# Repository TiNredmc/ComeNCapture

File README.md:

# ComeNCapture
This is very quick and dirty logic analyzer. Built with my sdcc template. https://github.com/TiNredmc/stm8l_sdcc_template/tree/master/code/ComeNCapture

# The Concept
<>

# Project status

Work in progress.

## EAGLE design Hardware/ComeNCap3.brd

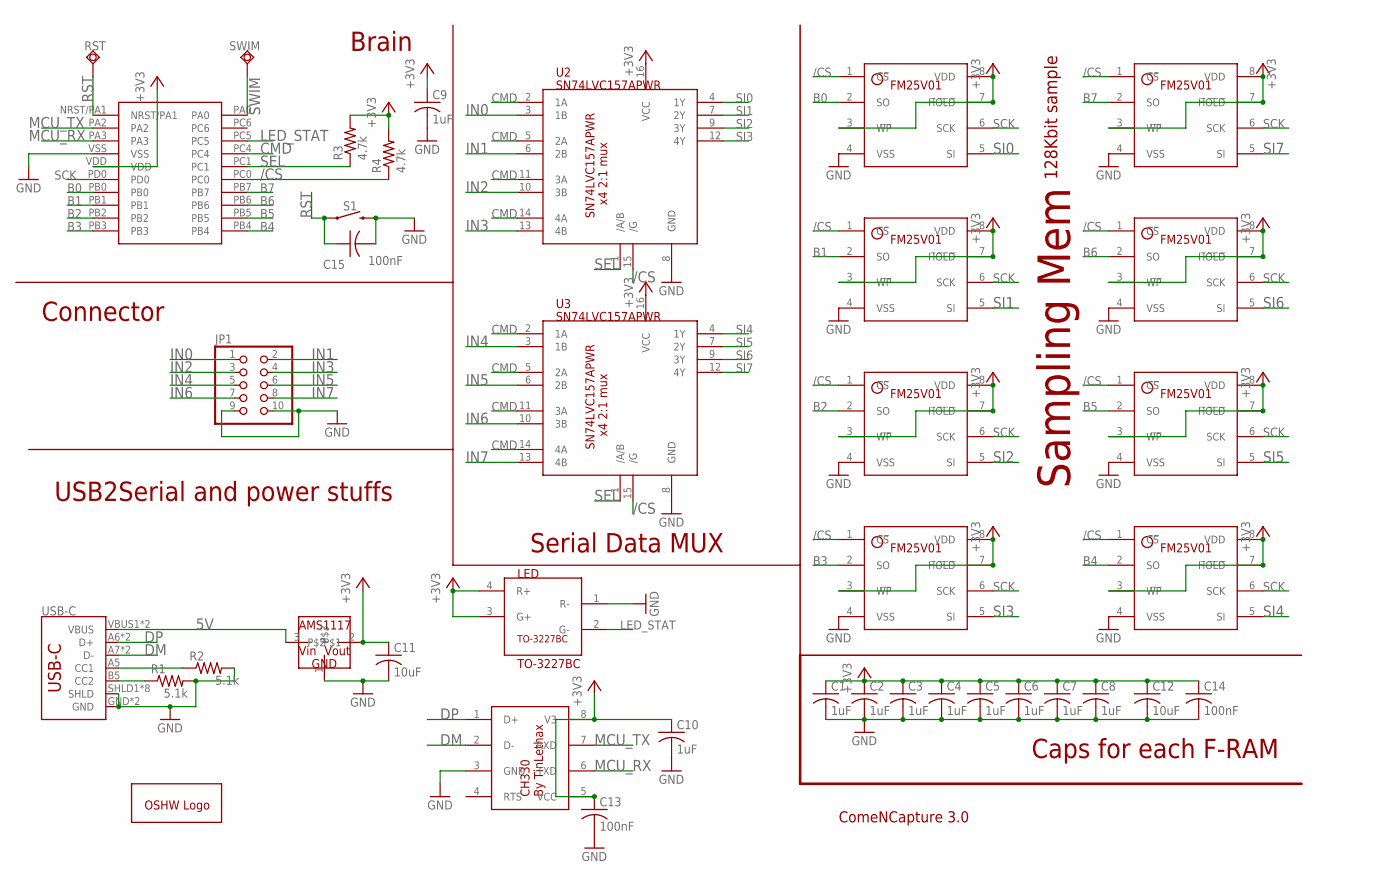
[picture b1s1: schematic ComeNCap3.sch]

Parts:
C1, C2, C3, C4, C5, C6, C7, C8, C9, C10: 1uF; C0603
C11, C12: 10uF; C0805
C13, C14, C15: 100nF; C1206
GOLD_ORB_SM1: OSHWLOGOLOGO5MM; OSHW_5MM
JP1: PINHD-2X5; 2X05
LED: TO-3227BC; DIODFN320X270X40-4L
M0, M1, M2, M3, M4, M5, M6, M7: FM25V01; SOIC127P601X172-8N
R1, R2: 5.1k; R0603
R3, R4: 4.7k; R0603
RST: TPSQTP20R; TP20R
S1: MOMENTARY-SWITCH-SPST-SMD-5.2-REDUNDANT; TACTILE_SWITCH_SMD_5.2MM
SWIM: TPSQTP20R; TP20R
U1: STM8L151F3; UFQFPN-20
U2, U3: SN74LVC157APWR; SOP65P640X120-16L
U4: CH330; SOIC127P600X150-8N
U5: AMS1117; SOT223
USB-C: USB_C16PIN; USB-C-16P

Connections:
5V: U5.3, USB-C.VBUS1 (VBUS), USB-C.VBUS2 (VBUS)
+3V3: C1.1, C2.1, C3.1, C4.1, C5.1, C6.1, C7.1, C8.1, C9.1, C10.1, C11.1, C12.1, C13.1, C14.1, LED.3 (G+), LED.4 (R+), M0.3 (W̅P̅), M0.7 (H̅O̅L̅D̅), M0.8 (VDD), M1.3 (W̅P̅), M1.7 (H̅O̅L̅D̅), M1.8 (VDD), M2.3 (W̅P̅), M2.7 (H̅O̅L̅D̅), M2.8 (VDD), M3.3 (W̅P̅), M3.7 (H̅O̅L̅D̅), M3.8 (VDD), M4.3 (W̅P̅), M4.7 (H̅O̅L̅D̅), M4.8 (VDD), M5.3 (W̅P̅), M5.7 (H̅O̅L̅D̅), M5.8 (VDD), M6.3 (W̅P̅), M6.7 (H̅O̅L̅D̅), M6.8 (VDD), M7.3 (W̅P̅), M7.7 (H̅O̅L̅D̅), M7.8 (VDD), R3.2, R4.2, U1.VDD, U2.16 (VCC), U3.16 (VCC), U4.5 (VCC), U4.8 (V3), U5.2
/CS: M0.1 (C̅S̅), M1.1 (C̅S̅), M2.1 (C̅S̅), M3.1 (C̅S̅), M4.1 (C̅S̅), M5.1 (C̅S̅), M6.1 (C̅S̅), M7.1 (C̅S̅), R4.1, U1.PC0, U2.15 (/G), U3.15 (/G)
B0: M0.2 (SO), U1.PB0
B1: M1.2 (SO), U1.PB1
B2: M2.2 (SO), U1.PB2
B3: M3.2 (SO), U1.PB3
B4: M4.2 (SO), U1.PB4
B5: M5.2 (SO), U1.PB5
B6: M6.2 (SO), U1.PB6
B7: M7.2 (SO), U1.PB7
CMD: U1.PC4, U2.2 (1A), U2.5 (2A), U2.11 (3A), U2.14 (4A), U3.2 (1A), U3.5 (2A), U3.11 (3A), U3.14 (4A)
DM: U4.2 (D-), USB-C.A7 (D-), USB-C.B7 (D-)
DP: U4.1 (D+), USB-C.A6 (D+), USB-C.B6 (D+)
GND: C1.2, C2.2, C3.2, C4.2, C5.2, C6.2, C7.2, C8.2, C9.2, C10.2, C11.2, C12.2, C13.2, C14.2, C15.2, JP1.9, JP1.10, LED.1 (R-), M0.4 (VSS), M1.4 (VSS), M2.4 (VSS), M3.4 (VSS), M4.4 (VSS), M5.4 (VSS), M6.4 (VSS), M7.4 (VSS), R1.2, R2.2, S1.3 (2), S1.4 (2), U1.VSS, U2.8 (GND), U3.8 (GND), U4.3 (GND), U5.1, USB-C.GND, USB-C.GND2 (GND), USB-C.SHLD1 (SHLD), USB-C.SHLD2 (SHLD), USB-C.SHLD3 (SHLD), USB-C.SHLD4 (SHLD), USB-C.SHLD5 (SHLD), USB-C.SHLD6 (SHLD), USB-C.SHLD7 (SHLD), USB-C.SHLD8 (SHLD)
IN0: JP1.1, U2.3 (1B)
IN1: JP1.2, U2.6 (2B)
IN2: JP1.3, U2.10 (3B)
IN3: JP1.4, U2.13 (4B)
IN4: JP1.5, U3.3 (1B)
IN5: JP1.6, U3.6 (2B)
IN6: JP1.7, U3.10 (3B)
IN7: JP1.8, U3.13 (4B)
LED_STAT: LED.2 (G-), U1.PC5
MCU_RX: U1.PA3, U4.6 (TXD)
MCU_TX: U1.PA2, U4.7 (RXD)
unnamed: R2.1, USB-C.A5 (CC1)
unnamed: R1.1, USB-C.B5 (CC2)
RST: C15.1, RST.TP, S1.1, S1.2 (1), U1.NRST/PA1
SCK: M0.6 (SCK), M1.6 (SCK), M2.6 (SCK), M3.6 (SCK), M4.6 (SCK), M5.6 (SCK), M6.6 (SCK), M7.6 (SCK), U1.PD0
SEL: R3.1, U1.PC1, U2.1 (/A/B), U3.1 (/A/B)
SI0: M0.5 (SI), U2.4 (1Y)
SI1: M1.5 (SI), U2.7 (2Y)
SI2: M2.5 (SI), U2.9 (3Y)
SI3: M3.5 (SI), U2.12 (4Y)
SI4: M4.5 (SI), U3.4 (1Y)
SI5: M5.5 (SI), U3.7 (2Y)
SI6: M6.5 (SI), U3.9 (3Y)
SI7: M7.5 (SI), U3.12 (4Y)
SWIM: SWIM.TP, U1.PA0

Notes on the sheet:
Sampling Mem
128Kbit sample
ComeNCapture 3.0
Serial Data MUX
Brain
Connector
USB2Serial and power stuffs
Caps for each F-RAM

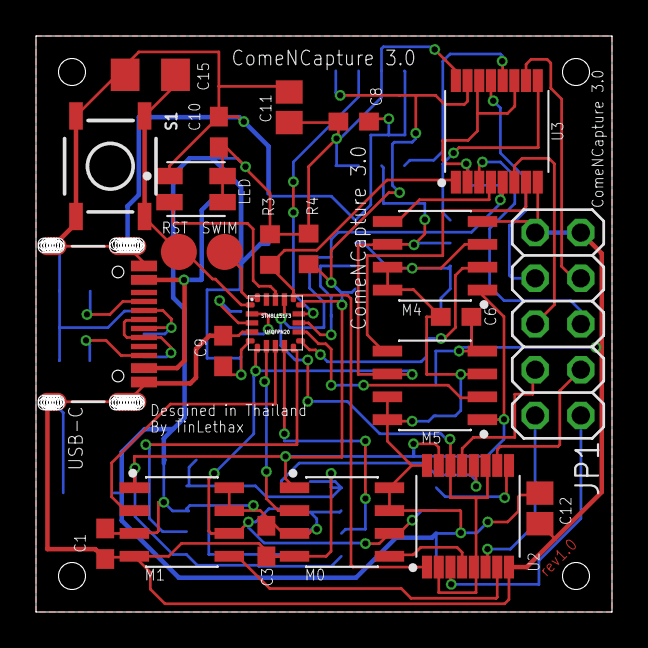
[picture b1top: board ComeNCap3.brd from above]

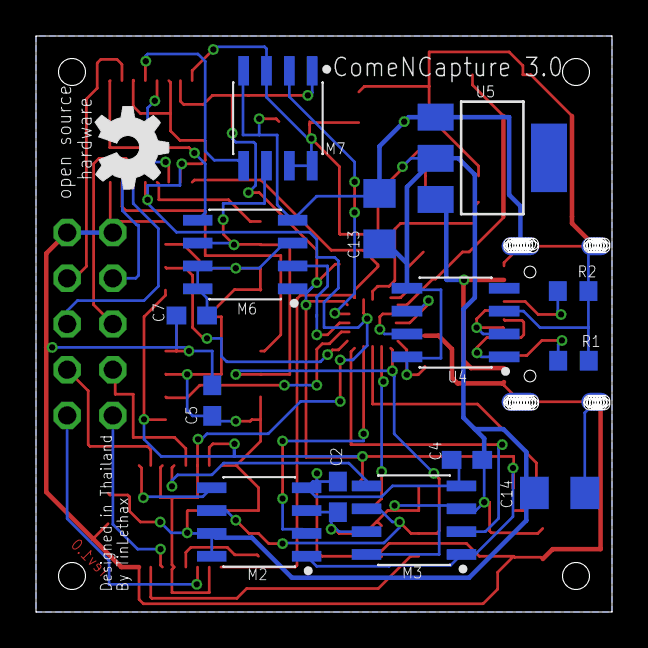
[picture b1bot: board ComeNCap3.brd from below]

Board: 2 copper layers, 32.0 x 32.0 mm, 39 parts (15 on the bottom side), 40 nets.

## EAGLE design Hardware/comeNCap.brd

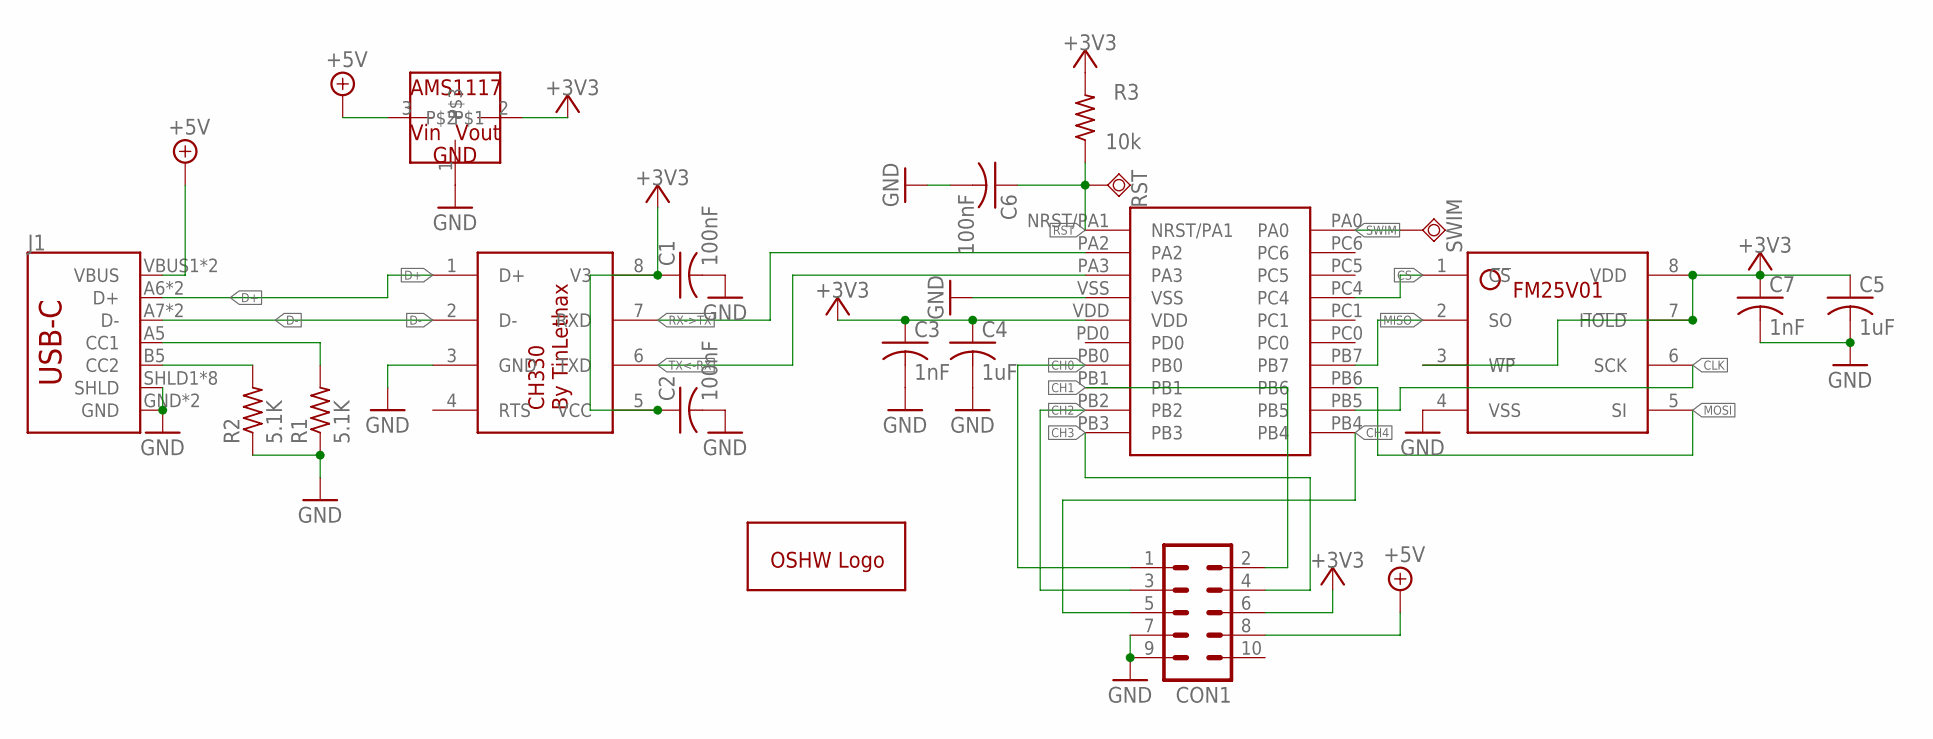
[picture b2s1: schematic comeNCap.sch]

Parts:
C1, C2, C6: 100nF; C1210
C3, C7: 1nF; C0805
C4, C5: 1uF; C0603
CON1: MA05-2
GOLD_ORB_SM1: OSHWLOGOLOGO5MM; OSHW_5MM
J1: USB_C16PIN; USB-C-16P
R1, R2: 5.1K; R0805
R3: 10k; R0805
RST: TPSQTP20R; TP20R
SWIM: TPSQTP20R; TP20R
U$1: STM8L151F3; UFQFPN-20
U$2: FM25V01; SOIC127P601X172-8N
U$3: CH330; SOIC127P600X150-8N
U$4: AMS1117; SOT223

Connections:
+3V3: C1.1, C2.1, C3.1, C4.1, C5.1, C7.1, CON1.6, R3.2, U$1.VDD, U$2.3 (W̅P̅), U$2.7 (H̅O̅L̅D̅), U$2.8 (VDD), U$3.5 (VCC), U$3.8 (V3), U$4.2
+5V: CON1.8, J1.VBUS1 (VBUS), J1.VBUS2 (VBUS), U$4.3
CH0: CON1.1, U$1.PB0
CH1: CON1.2, U$1.PB1
CH2: CON1.3, U$1.PB2
CH3: CON1.4, U$1.PB3
CH4: CON1.5, U$1.PB4
CLK: U$1.PB5, U$2.6 (SCK)
CS: U$1.PC4, U$2.1 (C̅S̅)
D+: J1.A6 (D+), J1.B6 (D+), U$3.1 (D+)
D-: J1.A7 (D-), J1.B7 (D-), U$3.2 (D-)
GND: C1.2, C2.2, C3.2, C4.2, C5.2, C6.2, C7.2, CON1.7, CON1.9, J1.GND, J1.GND2 (GND), J1.SHLD1 (SHLD), J1.SHLD2 (SHLD), J1.SHLD3 (SHLD), J1.SHLD4 (SHLD), J1.SHLD5 (SHLD), J1.SHLD6 (SHLD), J1.SHLD7 (SHLD), J1.SHLD8 (SHLD), R1.1, R2.1, U$1.VSS, U$2.4 (VSS), U$3.3 (GND), U$4.1
MISO: U$1.PB7, U$2.2 (SO)
MOSI: U$1.PB6, U$2.5 (SI)
unnamed: J1.A5 (CC1), R1.2
unnamed: J1.B5 (CC2), R2.2
RST: C6.1, R3.1, RST.TP, U$1.NRST/PA1
RX->TX: U$1.PA2, U$3.7 (RXD)
SWIM: SWIM.TP, U$1.PA0
TX<-RX: U$1.PA3, U$3.6 (TXD)

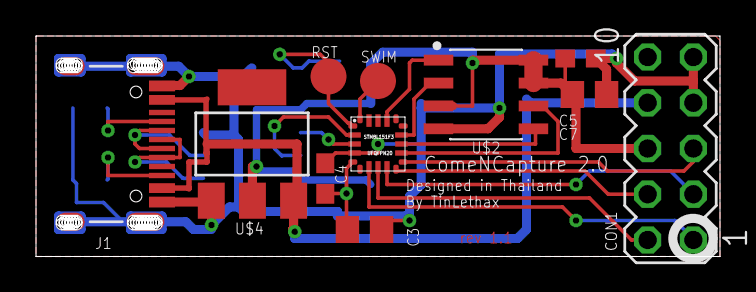
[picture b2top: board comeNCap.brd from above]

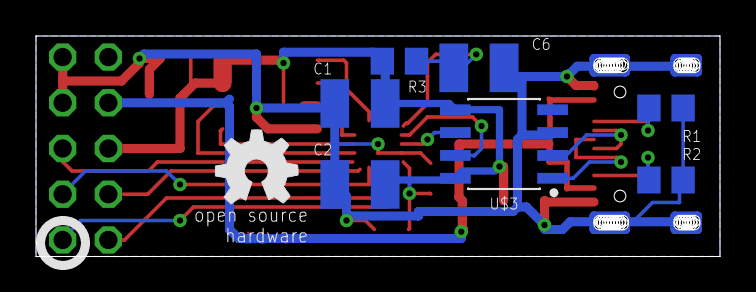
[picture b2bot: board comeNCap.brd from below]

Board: 2 copper layers, 38.0 x 12.2 mm, 19 parts (8 on the bottom side), 20 nets.

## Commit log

2020-05-23 The source file
2020-05-24 Make it a bit lighter
2021-08-11 HW readme
2021-08-11 added HW files
2021-08-11 Go get the latest version at my STM8L repo
    https://github.com/TiNredmc/stm8l_sdcc_template
2021-08-11 Will update later
2021-09-22 ComeNCapture 3.0 rev1.0
    Coming soon.

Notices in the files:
parts and their libraries:
SparkFun-Switches: Licensing: Creative Commons ShareAlike 4.0 International - https://creativecommons.org/licenses/by-sa/4.0
